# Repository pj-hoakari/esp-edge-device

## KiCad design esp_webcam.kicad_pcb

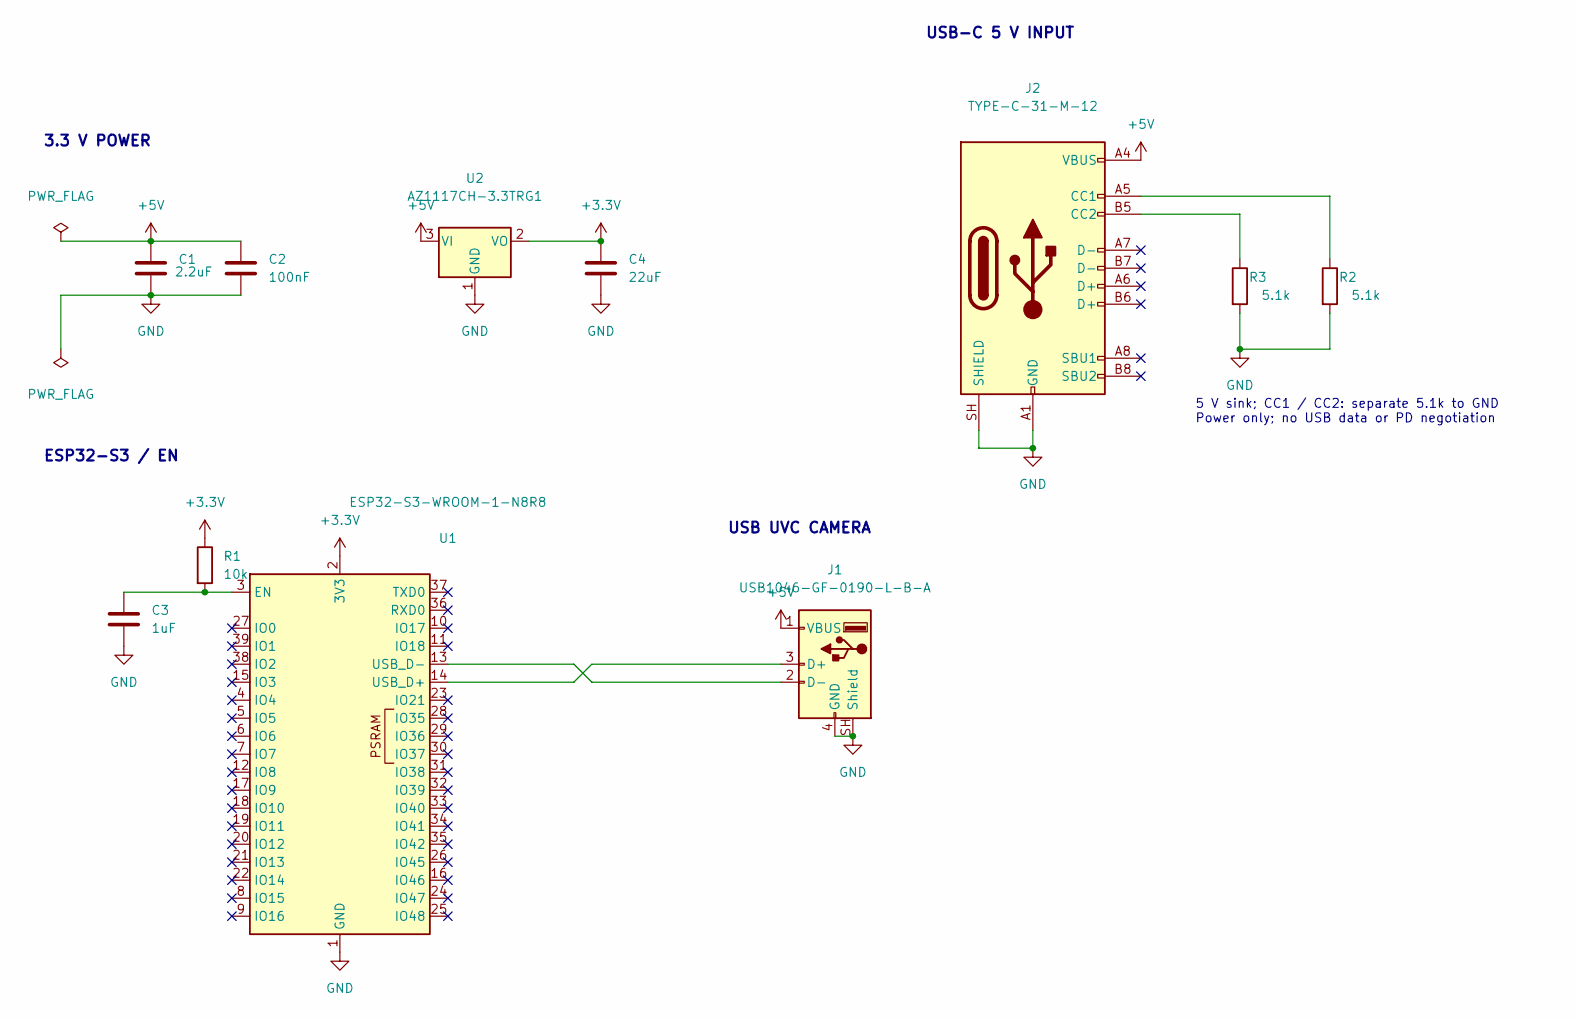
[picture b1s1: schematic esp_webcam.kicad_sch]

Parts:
C1: 2.2uF; C_0603_1608Metric; Voltage 16V; Tolerance 10%; MPN CL10A225KO8NNNC; LCSC C23630
C2: 100nF; C_0603_1608Metric; Voltage 50V; Tolerance 10%; MPN CL10B104KB8NNNC; LCSC C1591
C3: 1uF; C_0603_1608Metric; Voltage 50V; Tolerance 10%; MPN CL10A105KB8NNNC; LCSC C15849
C4: 22uF; C_0805_2012Metric; Voltage 25V; Tolerance 20%; MPN CL21A226MAQNNNE; LCSC C45783
J1: USB1046-GF-0190-L-B-A; USB_A_Receptacle_GCT_USB1046; MPN USB1046-GF-0190-L-B-A; LCSC C6307429
J2: TYPE-C-31-M-12; USB_C_Receptacle_HRO_TYPE-C-31-M-12; MPN TYPE-C-31-M-12; LCSC C165948
R1: 10k; R_0603_1608Metric; Tolerance 1%; MPN 0603WAF1002T5E; LCSC C25804
R2, R3: 5.1k; R_0603_1608Metric; Tolerance 1%; MPN 0603WAF5101T5E; LCSC C23186
U1: ESP32-S3-WROOM-1-N8R8; ESP32-S3-WROOM-1; MPN ESP32-S3-WROOM-1-N8R8; LCSC C2913201
U2: AZ1117CH-3.3TRG1; SOT-223-3_TabPin2; MPN AZ1117CH-3.3TRG1; LCSC C92102

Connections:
+3.3V: C4.1, R1.1, U1.2 (3V3), U2.2 (VO)
+5V: C1.1, C2.1, J1.1 (VBUS), J2.A4 (VBUS), J2.A9 (VBUS), J2.B4 (VBUS), J2.B9 (VBUS), U2.3 (VI)
GND: C1.2, C2.2, C3.2, C4.2, J1.4 (GND), J1.SH (Shield), J2.A1 (GND), J2.A12 (GND), J2.B1 (GND), J2.B12 (GND), J2.SH (SHIELD), R2.2, R3.2, U1.1 (GND), U1.40 (GND), U1.41 (GND), U2.1 (GND)
unnamed: J1.3 (D+), U1.14 (USB_D+)
unnamed: J1.2 (D-), U1.13 (USB_D-)
unnamed: J2.A5 (CC1), R2.1
unnamed: J2.B5 (CC2), R3.1
unnamed: C3.1, R1.2, U1.3 (EN)

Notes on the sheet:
ESP32-S3 / EN
3.3 V POWER
USB UVC CAMERA
5 V sink; CC1 / CC2: separate 5.1k to GND Power only; no USB data or PD negotiation
USB-C 5 V INPUT

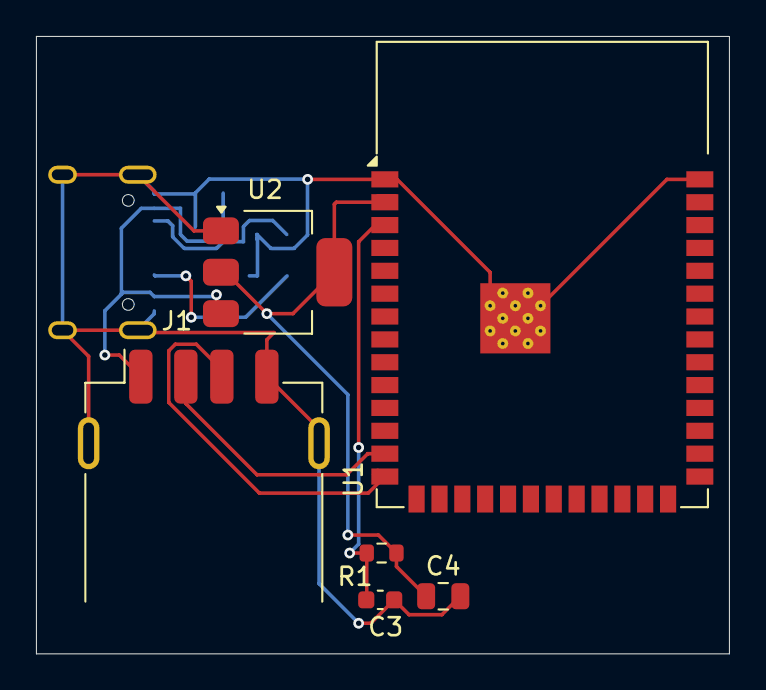
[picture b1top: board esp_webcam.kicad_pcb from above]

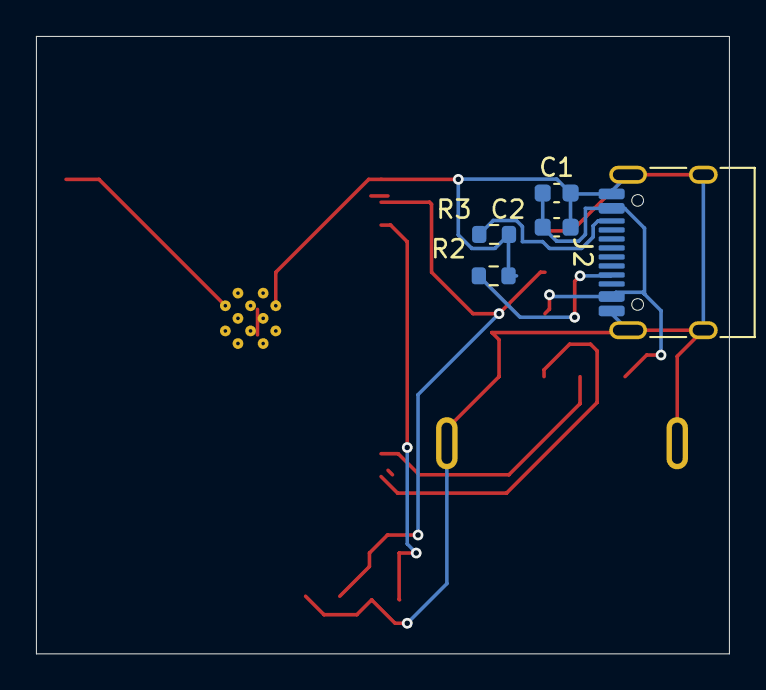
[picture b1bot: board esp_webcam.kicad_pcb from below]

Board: 2 copper layers, 38.5 x 34.3 mm, 11 parts (5 on the bottom side), 8 nets.

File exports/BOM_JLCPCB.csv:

Comment,Designator,Footprint,LCSC Part #,Manufacturer,MPN,Quantity
2.2uF,C1,C_0603_1608Metric,C23630,Samsung Electro-Mechanics,CL10A225KO8NNNC,1
100nF,C2,C_0603_1608Metric,C1591,Samsung Electro-Mechanics,CL10B104KB8NNNC,1
1uF,C3,C_0603_1608Metric,C15849,Samsung Electro-Mechanics,CL10A105KB8NNNC,1
22uF,C4,C_0805_2012Metric,C45783,Samsung Electro-Mechanics,CL21A226MAQNNNE,1
10k,R1,R_0603_1608Metric,C25804,UNI-ROYAL,0603WAF1002T5E,1
5.1k,"R2,R3",R_0603_1608Metric,C23186,UNI-ROYAL,0603WAF5101T5E,2
USB1046-GF-0190-L-B-A,J1,USB_A_Receptacle_GCT_USB1046,C6307429,Global Connector Technology,USB1046-GF-0190-L-B-A,1
TYPE-C-31-M-12,J2,USB_C_Receptacle_HRO_TYPE-C-31-M-12,C165948,Korean Hroparts Elec,TYPE-C-31-M-12,1
ESP32-S3-WROOM-1-N8R8,U1,ESP32-S3-WROOM-1,C2913201,Espressif Systems,ESP32-S3-WROOM-1-N8R8,1
AZ1117CH-3.3TRG1,U2,SOT-223-3_TabPin2,C92102,Diodes Incorporated,AZ1117CH-3.3TRG1,1
